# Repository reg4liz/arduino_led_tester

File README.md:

# arduino_led_tester
LED tester on atmega328 with adjustable current source.

## Glorious prototype

## Schematic

## Main components used for prototype
* [ATMEGA328P](https://www.digikey.com/en/products/detail/microchip-technology/ATMEGA328P-PU/1914589)
* [MCP6001 op-amp](https://www.digikey.com/es/products/detail/microchip-technology/MCP6001T-I-OT/551760)
* [SI2302CDS nmos](https://www.digikey.com/en/products/detail/vishay-siliconix/SI2302CDS-T1-GE3/1978729)
* [PEC12R-4025F-N0024 encoder](https://www.digikey.es/es/products/detail/bourns-inc/PEC12R-4025F-N0024/4499645)
* [ADS1115 ADC Module](https://aliexpress.com/item/1005006532275889.html)
* [MCP4725 DAC Module](https://aliexpress.com/item/1005007384695140.html)
* [SSD1306 128x64 OLED display](https://aliexpress.com/item/1005004355547926.html)

## TO-DO
* Full code re-write, at this time this is just a proof of concept to get it working quickly.
* Update components list.

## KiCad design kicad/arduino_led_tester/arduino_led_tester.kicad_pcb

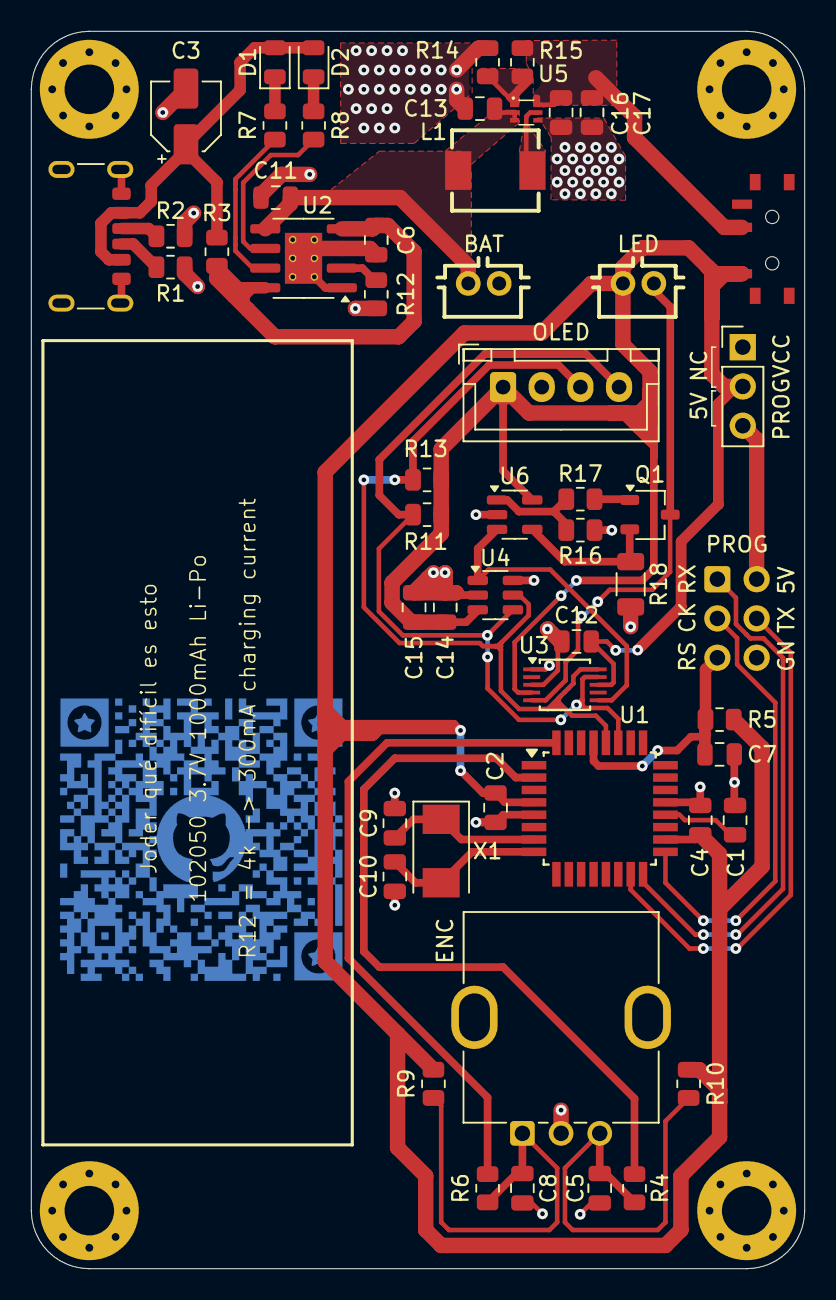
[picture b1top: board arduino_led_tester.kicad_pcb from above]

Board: 2 copper layers, 50.0 x 80.0 mm, 58 parts (0 on the bottom side), 32 nets.

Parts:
BAT: PH-2AWT; CONN-TH_B2B-PH-K-S
C1, C2, C4, C12, C14: 100n; C_0805_2012Metric
C3: 47u; CP_Elec_4x5.8
C5, C7, C8: 4n7; C_0805_2012Metric
C6, C11, C13, C15: 10u; C_0805_2012Metric
C9, C10: 22p; C_0805_2012Metric
C16, C17: 22u; C_0805_2012Metric
D1: Red; LED_0805_2012Metric
D2: Green; LED_0805_2012Metric
ENC: Encoder; RotaryEncoder_Bourns_Vertical_PEC12R-3x17F-Nxxxx
J1: TYPE-C 6P; USB_C_Receptacle_GCT_USB4125-xx-x-0190_6P_TopMnt_Horizontal
L1: 1u; IND-SMD_L5.5-W5.2
LED: CONN-TH_B2B-PH-K-S
MH1, MH2, MH3, MH4: M3; MountingHole_3.2mm_M3_Pad_Via
OLED: SSD1306; JST_XH_B4B-XH-A_1x04_P2.50mm_Vertical
PROG: AVR-ISP-6; IDC-Header_2x03_P2.54mm_Vertical
PROGVCC: Jumper; PinHeader_1x03_P2.54mm_Vertical
Q1: SI2302; TSOT-23
R1, R2: 5k1; R_0805_2012Metric
R3: 0R4; R_0805_2012Metric
R4, R5, R6, R9, R10: 10k; R_0805_2012Metric
R7, R8: 1k; R_0805_2012Metric
R11, R13: 4k7; R_0805_2012Metric
R12: 4k; R_0805_2012Metric
R14, R16: 100k; R_0805_2012Metric
R15: 732k; R_0805_2012Metric
R17: 100R; R_0805_2012Metric
R18: 50R; R_1206_3216Metric
SW2: SW_SPDT; Switch_SPDT_LCSC_MSK12CO2_BDM
U1: ATmega328PB-A; TQFP-32_7x7mm_P0.8mm
U2: TP4056-42-ESOP8; SOIC-8-1EP_3.9x4.9mm_P1.27mm_EP2.41x3.3mm_ThermalVias
U3: ADS1115IDGS; TSSOP-10_3x3mm_P0.5mm
U4: MCP4725; SOT-23-6
U5: TPS61023DRLR; SOT-563_L1.6-W1.2-P0.50-LS1.6-BR
U6: MCP6001-OT; SOT-23-5
X1: 16MHz; Crystal_SMD_Abracon_ABM3-2Pin_5.0x3.2mm

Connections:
+5V: C2.1, C4.1, C12.1, C14.1, C15.1, C16.1, C17.1, LED.2 (A), OLED.1 (VCC), PROGVCC.2, R5.1, R9.1, R10.1, R11.1, R13.1, R15.2, SW2.2 (B), SW2.3 (C), U1.4 (VCC), U1.18 (AVCC), U3.4 (AIN0), U3.8 (VDD), U4.3 (VDD), U5.6 (VOUT), U6.5 (V+)
+BATT: BAT.1, C11.1, C13.1, L1.1, U2.5 (BAT), U5.2 (EN), U5.3 (VIN)
+VBUS: C3.1, C6.1, D1.2 (A), D2.2 (A), J1.A9 (VBUS), J1.B9 (VBUS), R3.1, R3.2, U2.4 (V_{CC}), U2.8 (CE)
/AREF: C1.1, U1.20 (AREF)
/DACOUT: U3.6 (AIN2), U4.1 (VOUT), U6.3 (+)
/ENCA: R6.1, U1.32 (PD2)
/ENCB: R4.1, U1.2 (PD4)
/GATE: Q1.1 (G), R17.2
/LEDCATHODE: LED.1 (K), Q1.3 (D), U3.5 (AIN1)
/MISO: PROG.1 (MISO), U1.16 (PB4)
/MOSI: PROG.4 (MOSI), U1.15 (PB3)
/OPOUT: R16.2, R17.1, U6.1
/SCK: PROG.3 (SCK), U1.17 (PB5)
/SCL: OLED.3 (SCL), R13.2, U1.28 (PC5), U3.10 (SCL), U4.5 (SCL)
/SDA: OLED.4 (SDA), R11.2, U1.27 (PC4), U3.9 (SDA), U4.4 (SDA)
/SENSE: Q1.2 (S), R18.1, U6.4 (-)
/USBCC1: J1.A5 (CC1), R2.1
/USBCC2: J1.B5 (CC2), R1.1
/XTAL1: C9.1, U1.7 (XTAL1/PB6), X1.1
/XTAL2: C10.1, U1.8 (XTAL2/PB7), X1.2
/~RESET: C7.1, PROG.5 (~RST), R5.2, U1.29 (~RESET/PC6)
GND: BAT.2, C1.2, C2.2, C3.2, C4.2, C5.2, C6.2, C7.2, C8.2, C9.2, C10.2, C11.2, C12.2, C13.2, C14.2, C15.2, C16.2, C17.2, ENC.C, J1.A12 (GND), J1.B12 (GND), J1.S1 (SHIELD), MH1.1, MH2.1, MH3.1, MH4.1, OLED.2 (GND), PROG.6 (GND), R1.2, R2.2, R12.2, R14.2, R16.1, R18.2, U1.5 (GND), U1.21 (GND), U2.1 (TEMP), U2.3 (GND), U2.9 (EPAD), U3.1 (ADDR), U3.3 (GND), U4.2 (VSS), U4.6 (A0), U5.4 (GND), U6.2 (V-)
unnamed: C5.1, ENC.B, R4.2, R10.2
unnamed: C8.1, ENC.A, R6.2, R9.2
unnamed: D1.1 (K), R7.1
unnamed: D2.1 (K), R8.1
unnamed: PROG.2 (VCC), PROGVCC.3
unnamed: R12.1, U2.2 (PROG)
unnamed: R7.2, U2.7 (~CHRG)
unnamed: R8.2, U2.6 (~STDBY)
unnamed: R14.1, R15.1, U5.1 (FB)
unnamed: L1.2, U5.5 (SW)

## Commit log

2026-04-02 pcb design ready
    upload kicad files, schematics and gerbers
2026-04-02 updated readme
    include schematic and update to-do list
2026-04-02 converted gerbers to zip
2026-04-02 updates to cover pcb and fabrication files
